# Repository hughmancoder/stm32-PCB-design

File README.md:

# stm32-PCB-design

PCB board for `STM32F103C8T6` Microcontroller, a micro usb power supply, a regulator to power the mcu to 3.3V, and a crystal oscillator for the mcu. It has a reset switch to boot the board, a UART interface UART (Universal Asynchronous Receiver-Transmitter) to  uses two wires to exchange serial data between devices without a shared clock, as well as Serial Wire Debug (SWD) which is a  hardware interface designed by ARM for programming and debugging ARM-based microcontrollers using a st-link programmer. 

## Schematic
**Microcontroller and USB**

**Power Supply**

## Board

**3D view**

**layout**

## Manufacturing

Manufacturing gerber files, drill files, and Bill of Materials (BOM) are located in the `Manufacturing` folder.

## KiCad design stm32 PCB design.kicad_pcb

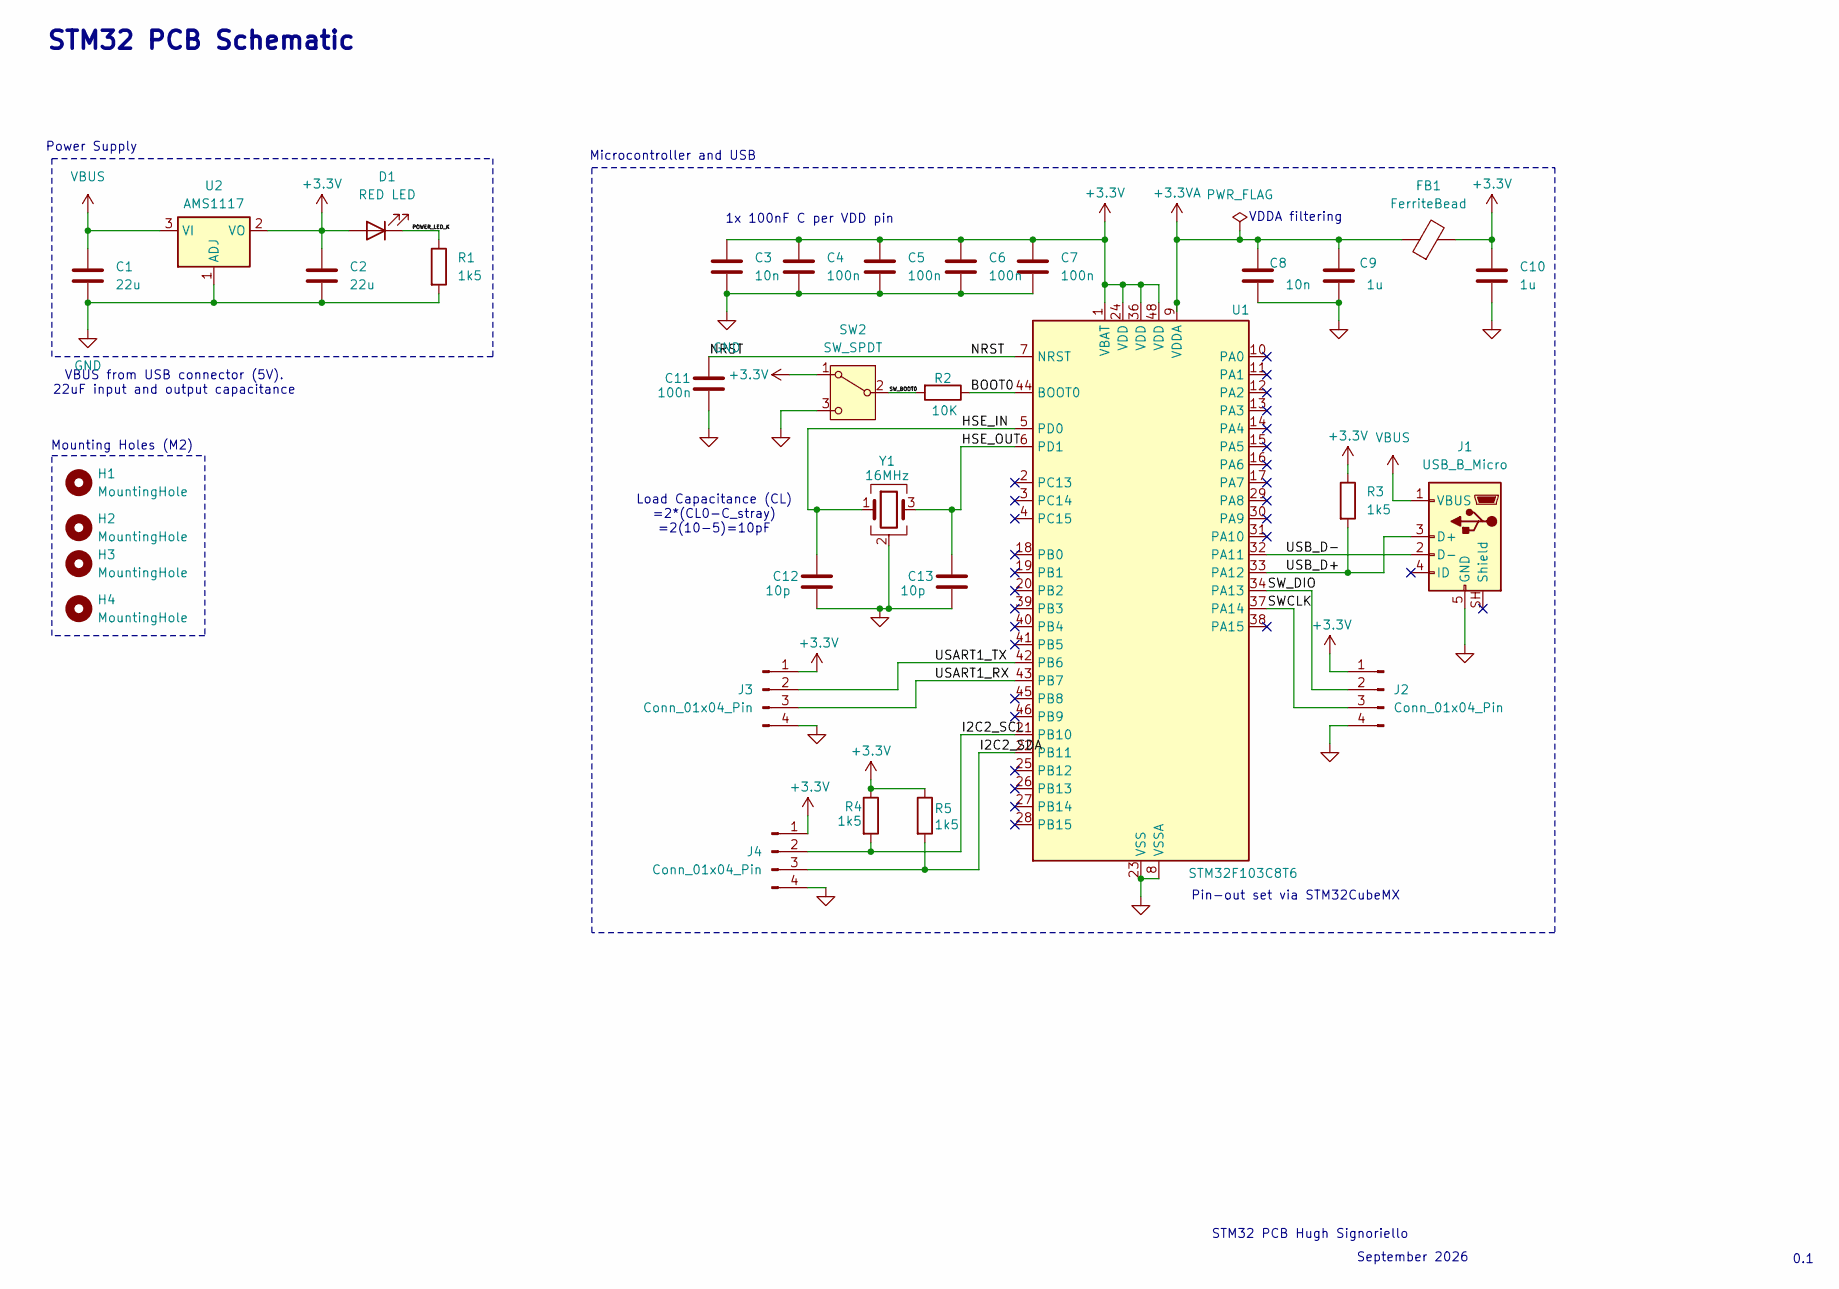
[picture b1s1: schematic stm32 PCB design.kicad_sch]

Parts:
C1, C2: 22u; C_0805_2012Metric
C3: 10n; C_0603_1608Metric
C4, C5, C6, C7, C11: 100n; C_01005_0402Metric
C8: 10n; C_01005_0402Metric
C9, C10: 1u; C_01005_0402Metric
C12, C13: 10p; C_01005_0402Metric
D1: RED LED; LED_0603_1608Metric_Pad1.05x0.95mm_HandSolder
FB1: FerriteBead; L_0603_1608Metric
H1, H2, H3, H4: MountingHole; MountingHole_2.2mm_M2
J1: USB_B_Micro; USB_Micro-B_Wuerth_629105150521
J2, J3, J4: Conn_01x04_Pin; PinHeader_1x04_P2.54mm_Vertical
R1, R3, R4, R5: 1k5; R_0402_1005Metric
R2: 10K; R_0402_1005Metric
SW2: SW_SPDT; SW_SPDT_PCM12
U1: STM32F103C8T6; LQFP-48_7x7mm_P0.5mm
U2: AMS1117; SOT-223-3_TabPin2
Y1: 16MHz; Crystal_SMD_3225-4Pin_3.2x2.5mm

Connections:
+3.3V: C2.1, C3.1, C4.1, C5.1, C6.1, C7.1, C10.1, D1.2 (A), FB1.2, J2.1, J3.1, J4.1, R3.1, R4.1, R5.1, SW2.1 (A), U1.1 (VBAT), U1.24 (VDD), U1.36 (VDD), U1.48 (VDD), U2.2 (VO)
+3.3VA: C8.1, C9.1, FB1.1, U1.9 (VDDA)
/BOOT0: R2.1, U1.44 (BOOT0)
/HSE_IN: C12.1, U1.5 (PD0), Y1.1
/HSE_OUT: C13.1, U1.6 (PD1), Y1.3
/I2C2_SCL: J4.2, R4.2, U1.21 (PB10)
/I2C2_SDA: J4.3, R5.2, U1.22 (PB11)
/NRST: C11.1, U1.7 (NRST)
/POWER_LED_K: D1.1 (K), R1.1
/SWCLK: J2.3, U1.37 (PA14)
/SW_BOOT0: R2.2, SW2.2 (B)
/SW_DIO: J2.2, U1.34 (PA13)
/USART1_RX: J3.3, U1.43 (PB7)
/USART1_TX: J3.2, U1.42 (PB6)
/USB_D+: J1.3 (D+), R3.2, U1.33 (PA12)
/USB_D-: J1.2 (D-), U1.32 (PA11)
GND: C1.2, C2.2, C3.2, C4.2, C5.2, C6.2, C7.2, C8.2, C9.2, C10.2, C11.2, C12.2, C13.2, J1.5 (GND), J2.4, J3.4, J4.4, R1.2, SW2.3 (C), U1.8 (VSSA), U1.23 (VSS), U1.35 (VSS), U1.47 (VSS), U2.1 (ADJ), Y1.2 (G), Y1.4 (G)
VBUS: C1.1, J1.1 (VBUS), U2.3 (VI)

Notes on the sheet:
VDDA filtering
VBUS from USB connector (5V). 22uF input and output capacitance
Power Supply
Microcontroller and USB
1x 100nF C per VDD pin
Pin-out set via STM32CubeMX
0.1
September 2026
STM32 PCB Hugh Signoriello
Load Capacitance (CL) =2*(CL0-C_stray) =2(10-5)=10pF
Mounting Holes (M2)
STM32 PCB Schematic

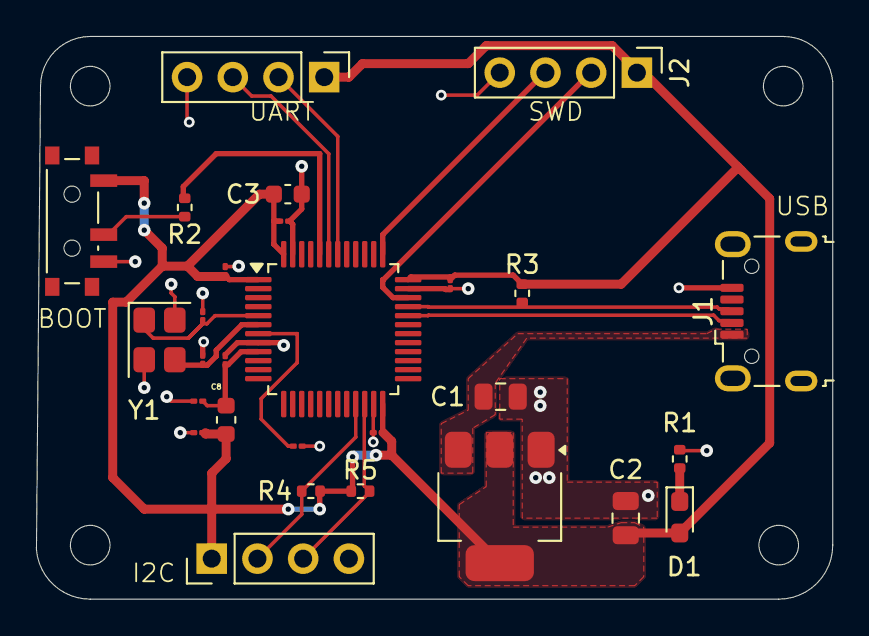
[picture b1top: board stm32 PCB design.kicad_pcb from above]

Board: 2 copper layers, 44.2 x 31.3 mm, 32 parts (0 on the bottom side), 18 nets.

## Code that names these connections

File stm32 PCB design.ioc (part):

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Mcu.Name=STM32F103C(8-B)Tx
Mcu.Package=LQFP48
Mcu.UserName=STM32F103C8Tx
PA11.Mode=Device
PA11.Signal=USB_DM
PA12.Mode=Device
PA12.Signal=USB_DP
PA13.Mode=Serial_Wire
PA13.Signal=SYS_JTMS-SWDIO
PA14.Mode=Serial_Wire
PA14.Signal=SYS_JTCK-SWCLK
PB10.Mode=I2C
PB10.Signal=I2C2_SCL
PB11.Mode=I2C
PB11.Signal=I2C2_SDA
PB6.Mode=Asynchronous
PB6.Signal=USART1_TX
PB7.Mode=Asynchronous
PB7.Signal=USART1_RX
PD0-OSC_IN.Mode=HSE-External-Oscillator
PD0-OSC_IN.Signal=RCC_OSC_IN
PD1-OSC_OUT.Mode=HSE-External-Oscillator
PD1-OSC_OUT.Signal=RCC_OSC_OUT
RCC.SYSCLKFreq_VALUE=48000000
RCC.SYSCLKSource=RCC_SYSCLKSOURCE_PLLCLK
board=custom
